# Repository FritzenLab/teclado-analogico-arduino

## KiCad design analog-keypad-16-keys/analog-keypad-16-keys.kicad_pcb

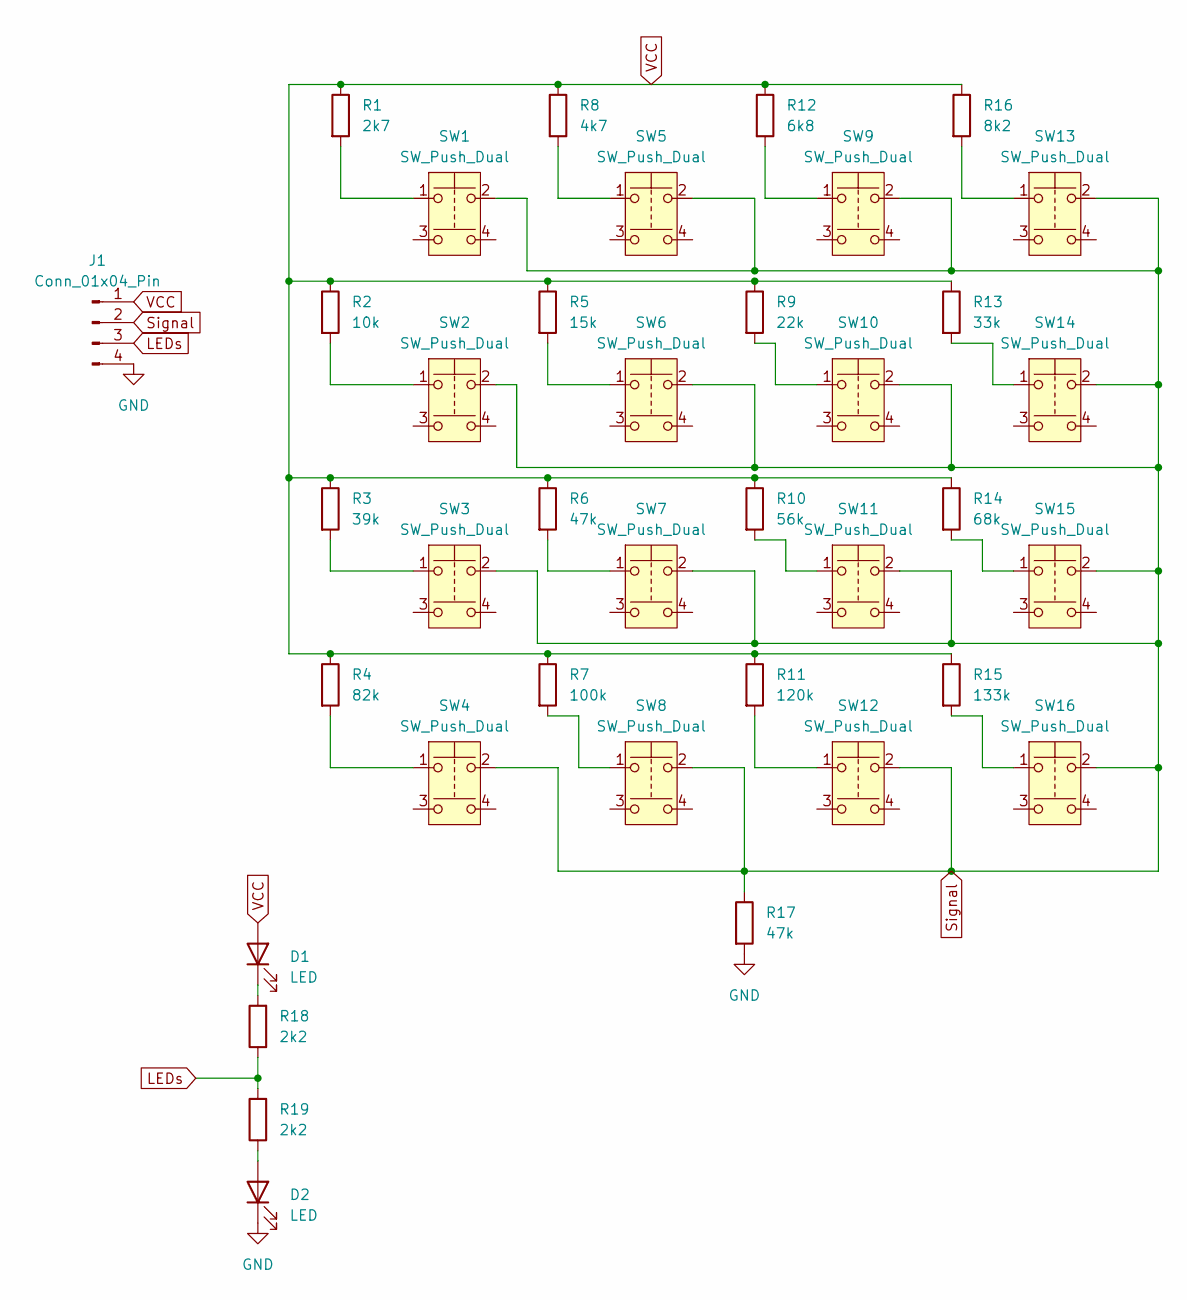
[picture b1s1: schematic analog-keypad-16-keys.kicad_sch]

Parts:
D1, D2: LED; LED_D5.0mm_Clear
J1: Conn_01x04_Pin; PinHeader_1x04_P2.54mm_Vertical
R1: 2k7; R_0805_2012Metric
R2: 10k; R_0805_2012Metric
R3: 39k; R_0805_2012Metric
R4: 82k; R_0805_2012Metric
R5: 15k; R_0805_2012Metric
R6, R17: 47k; R_0805_2012Metric
R7: 100k; R_0805_2012Metric
R8: 4k7; R_0805_2012Metric
R9: 22k; R_0805_2012Metric
R10: 56k; R_0805_2012Metric
R11: 120k; R_0805_2012Metric
R12: 6k8; R_0805_2012Metric
R13: 33k; R_0805_2012Metric
R14: 68k; R_0805_2012Metric
R15: 133k; R_0805_2012Metric
R16: 8k2; R_0805_2012Metric
R18, R19: 2k2; R_0805_2012Metric
SW1, SW2, SW3, SW4, SW5, SW6, SW7, SW8, SW9, SW10, SW11, SW12, SW13, SW14, SW15, SW16: SW_Push_Dual; SW_PUSH_6mm

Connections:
GND: D2.1 (K), J1.4, R17.2
LEDs: J1.3, R18.1, R19.2
unnamed: D1.1 (K), R18.2
unnamed: D2.2 (A), R19.1
unnamed: R1.2, SW1.1
unnamed: R2.2, SW2.1
unnamed: R3.2, SW3.1
unnamed: R4.2, SW4.1
unnamed: R5.2, SW6.1
unnamed: R6.2, SW7.1
unnamed: R7.2, SW8.1
unnamed: R8.2, SW5.1
unnamed: R9.2, SW10.1
unnamed: R10.2, SW11.1
unnamed: R11.2, SW12.1
unnamed: R12.2, SW9.1
unnamed: R13.2, SW14.1
unnamed: R14.2, SW15.1
unnamed: R15.2, SW16.1
unnamed: R16.2, SW13.1
Signal: J1.2, R17.1, SW1.2, SW2.2, SW3.2, SW4.2, SW5.2, SW6.2, SW7.2, SW8.2, SW9.2, SW10.2, SW11.2, SW12.2, SW13.2, SW14.2, SW15.2, SW16.2
VCC: D1.2 (A), J1.1, R1.1, R2.1, R3.1, R4.1, R5.1, R6.1, R7.1, R8.1, R9.1, R10.1, R11.1, R12.1, R13.1, R14.1, R15.1, R16.1

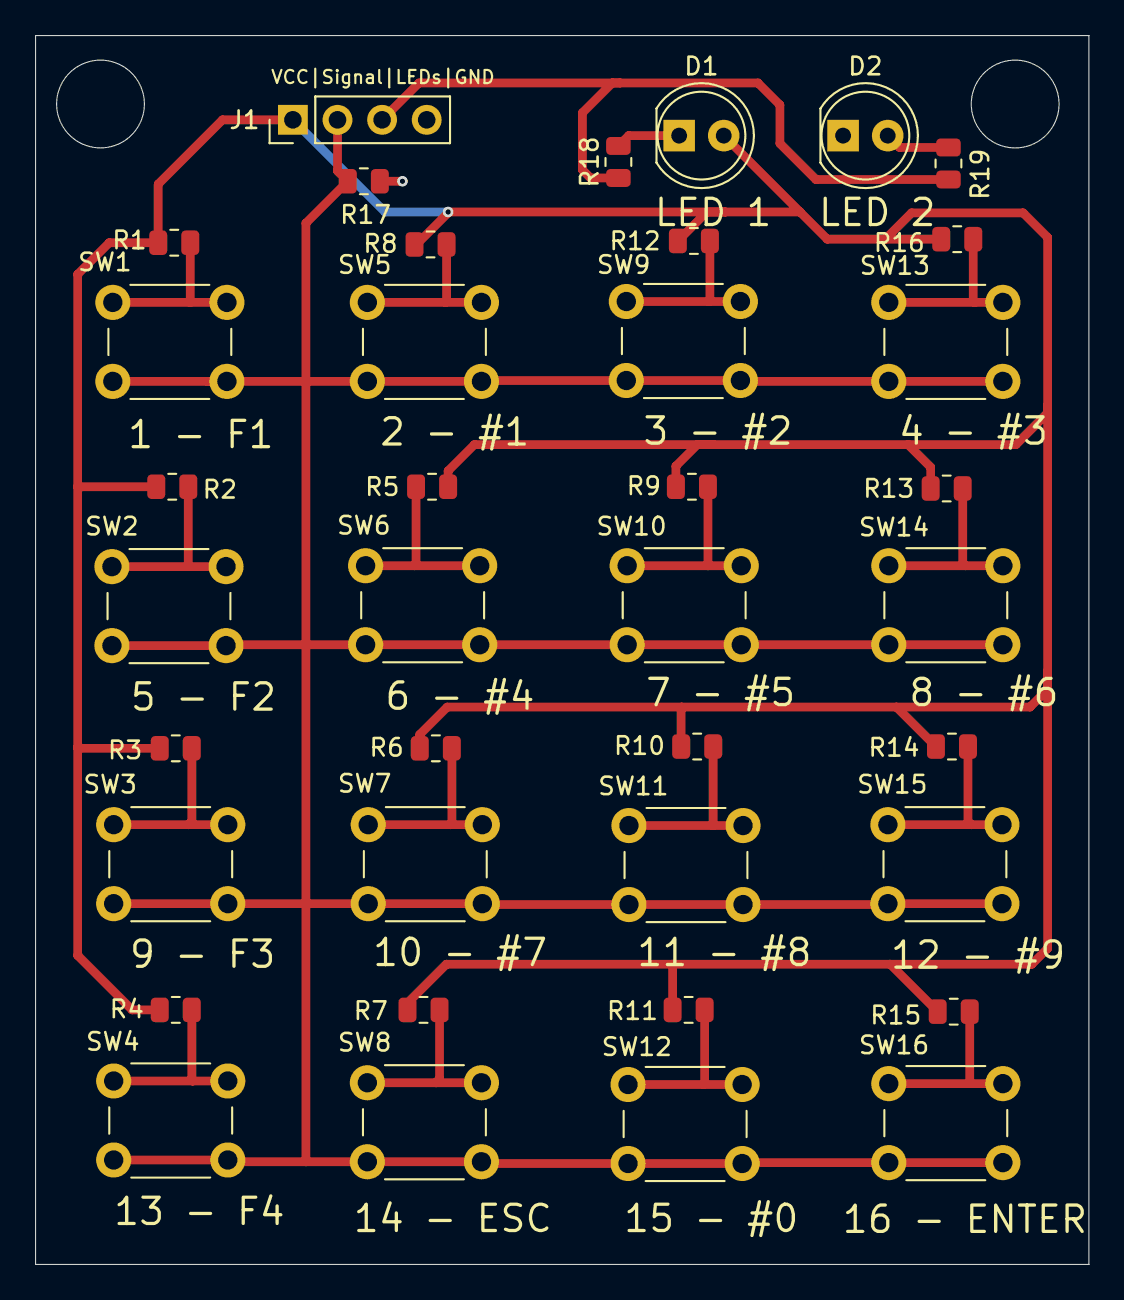
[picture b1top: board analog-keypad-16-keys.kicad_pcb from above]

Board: 2 copper layers, 60.0 x 70.0 mm, 38 parts (0 on the bottom side), 22 nets.

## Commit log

2016-12-05 upload inicial - sketch e esquematico
    Sketch e esquemático do teclado analógico com Arduino UNO
2024-10-16 Added schematics and PCB
2024-10-16 started schematic capture
2024-10-17 schematic finished, PCB started
    schematic finished, PCB started
2024-10-17 backup
2024-10-17 Started PCB layout
2024-10-17 finished PCB
2024-10-18 backups
2024-10-18 Gerber generated
